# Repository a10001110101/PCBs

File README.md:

# PCBs
Various gerbers and other files for PCB design

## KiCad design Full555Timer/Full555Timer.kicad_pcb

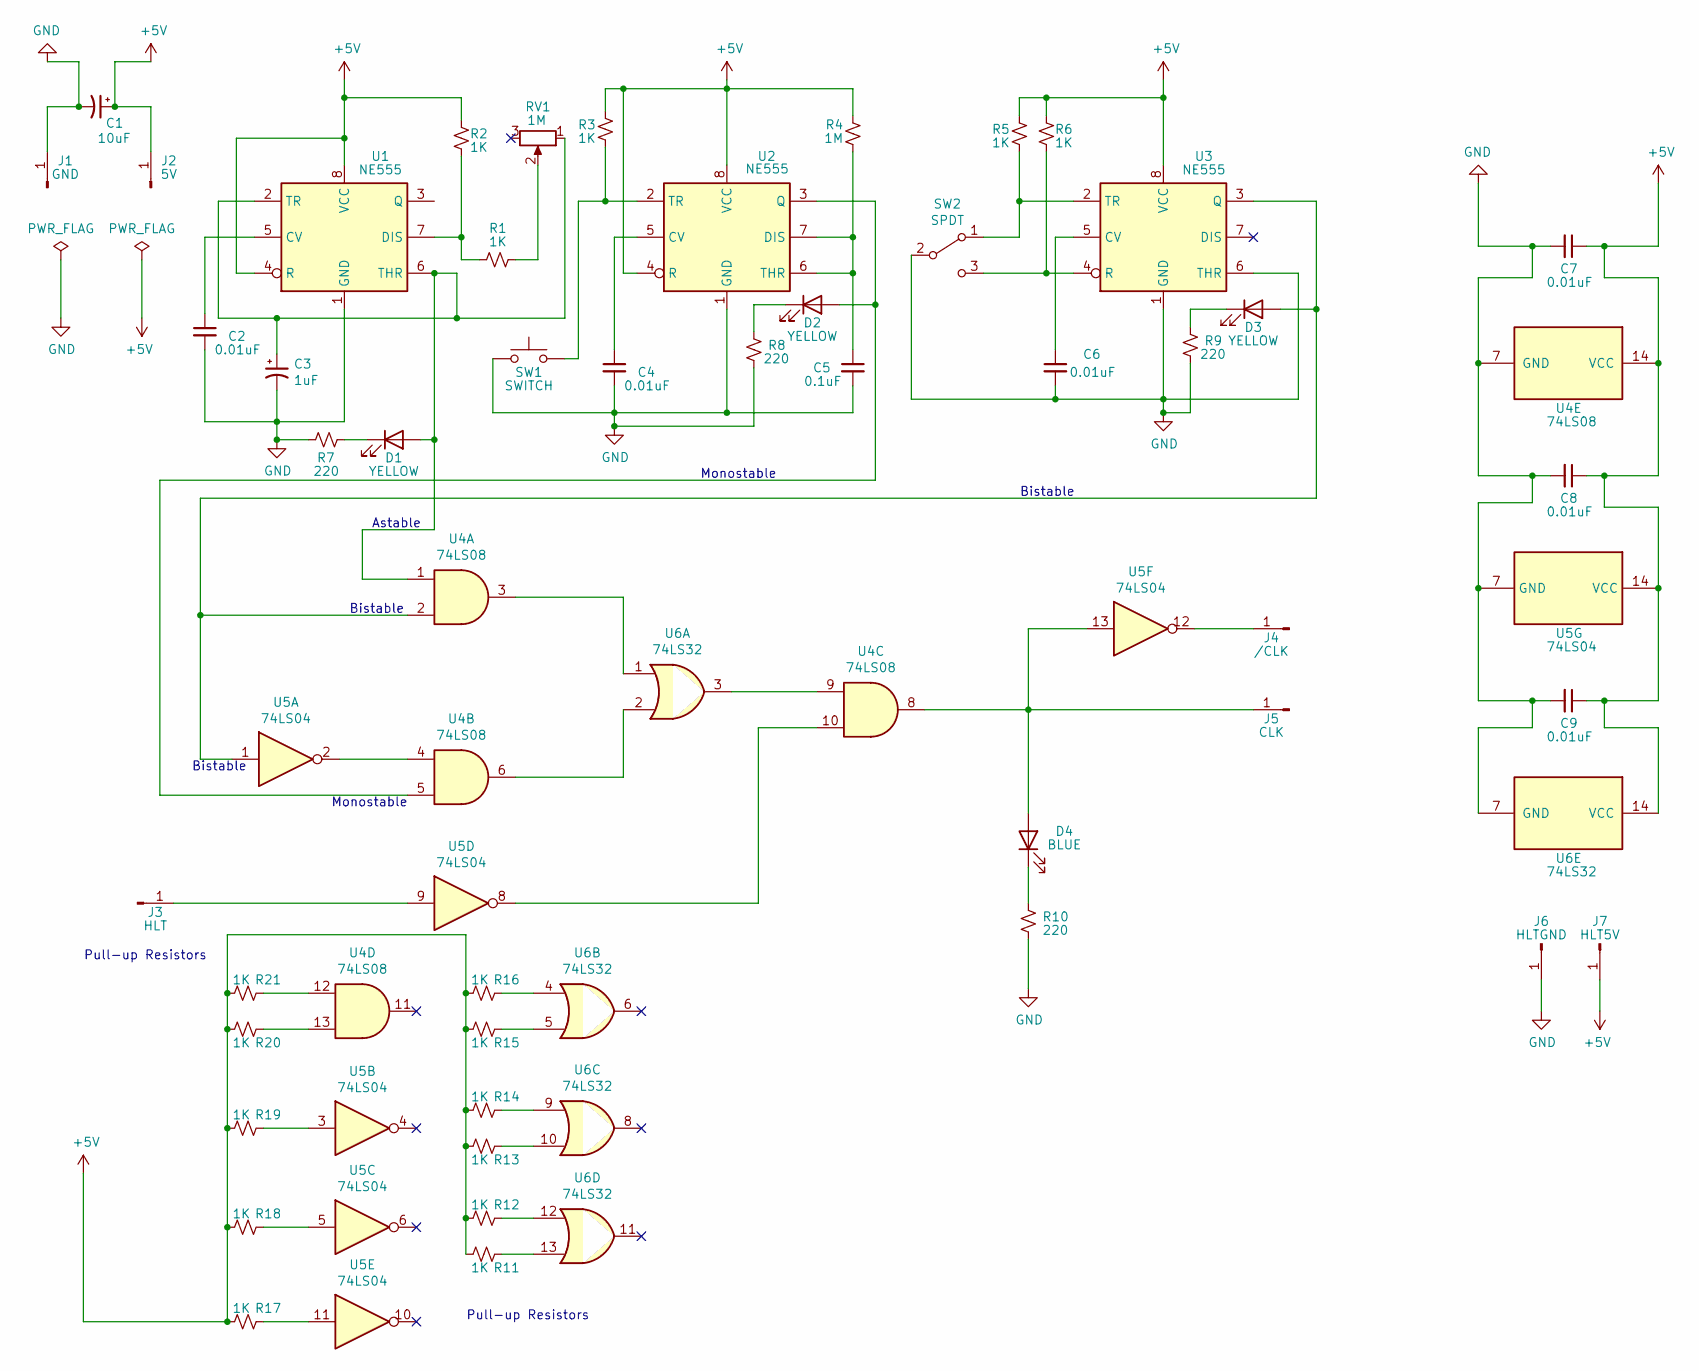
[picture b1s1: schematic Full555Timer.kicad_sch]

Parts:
C1: 10uF; CP_Radial_D6.3mm_P2.50mm
C2, C4, C6, C7, C8, C9: 0.01uF; C_Disc_D6.0mm_W2.5mm_P5.00mm
C3: 1uF; CP_Radial_D5.0mm_P2.50mm
C5: 0.1uF; C_Disc_D4.7mm_W2.5mm_P5.00mm
D1, D2, D3: YELLOW; LED_D3.0mm
D4: BLUE; LED_D3.0mm
J1: GND; PinHeader_1x01_P1.00mm_Vertical
J2: 5V; PinHeader_1x01_P1.00mm_Vertical
J3: HLT; PinHeader_1x01_P1.00mm_Vertical
J4: /CLK; PinHeader_1x01_P1.00mm_Vertical
J5: CLK; PinHeader_1x01_P1.00mm_Vertical
J6: HLTGND; PinHeader_1x01_P1.00mm_Vertical
J7: HLT5V; PinHeader_1x01_P1.00mm_Vertical
R1, R2, R3, R5, R6, R11, R12, R13, R14, R15, R16, R17, R18, R19, R20, R21: 1K; R_Axial_DIN0207_L6.3mm_D2.5mm_P10.16mm_Horizontal
R4: 1M; R_Axial_DIN0207_L6.3mm_D2.5mm_P10.16mm_Horizontal
R7, R8, R9, R10: 220; R_Axial_DIN0207_L6.3mm_D2.5mm_P10.16mm_Horizontal
RV1: 1M; Potentiometer_Bourns_3386C_Horizontal
SW1: SWITCH; B3F-1000
SW2: SPDT; SW_SS-12E17
U1, U2, U3: NE555; DIP-8_W7.62mm
U4: 74LS08; DIP-14_W7.62mm
U5: 74LS04; DIP-14_W7.62mm
U6: 74LS32; DIP-14_W7.62mm

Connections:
+5V: C1.1, C7.1, C8.1, C9.1, J2.1, J7.1, R2.2, R3.2, R4.2, R5.2, R6.2, R11.2, R12.2, R13.2, R14.2, R15.2, R16.2, R17.2, R18.2, R19.2, R20.2, R21.2, U1.4 (R), U1.8 (VCC), U2.4 (R), U2.8 (VCC), U3.8 (VCC), U4.14 (VCC), U5.14 (VCC), U6.14 (VCC)
GND: C1.2, C2.2, C3.2, C4.2, C5.2, C6.2, C7.2, C8.2, C9.2, J1.1, J6.1, R7.1, R8.2, R9.2, R10.2, SW1.1, SW2.2 (B), U1.1 (GND), U2.1 (GND), U3.1 (GND), U3.6 (THR), U4.7 (GND), U5.7 (GND), U6.7 (GND)
unnamed: C2.1, U1.5 (CV)
unnamed: C4.1, U2.5 (CV)
unnamed: C5.1, R4.1, U2.6 (THR), U2.7 (DIS)
unnamed: C6.1, U3.5 (CV)
unnamed: D1.1 (K), R7.2
unnamed: D2.1 (K), R8.1
unnamed: D2.2 (A), U2.3 (Q), U4.5
unnamed: D3.1 (K), R9.1
unnamed: D3.2 (A), U3.3 (Q), U4.2, U5.1
unnamed: D4.1 (K), R10.1
unnamed: D4.2 (A), J5.1, U4.8, U5.13
unnamed: J3.1, U5.9
unnamed: J4.1, U5.12
unnamed: R1.1, RV1.2
unnamed: R1.2, R2.1, U1.7 (DIS)
unnamed: R3.1, SW1.2, U2.2 (TR)
unnamed: R5.1, SW2.1 (A), U3.2 (TR)
unnamed: R6.1, SW2.3 (C), U3.4 (R)
unnamed: R11.1, U6.13
unnamed: R12.1, U6.12
unnamed: R13.1, U6.10
unnamed: R14.1, U6.9
unnamed: R15.1, U6.5
unnamed: R16.1, U6.4
unnamed: R17.1, U5.11
unnamed: R18.1, U5.5
unnamed: R19.1, U5.3
unnamed: R20.1, U4.13
unnamed: R21.1, U4.12
unnamed: U4.3, U6.1
unnamed: U4.4, U5.2
unnamed: U4.6, U6.2
unnamed: U4.9, U6.3
unnamed: U4.10, U5.8

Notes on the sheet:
Monostable
Astable
Bistable
Pull-up Resistors

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
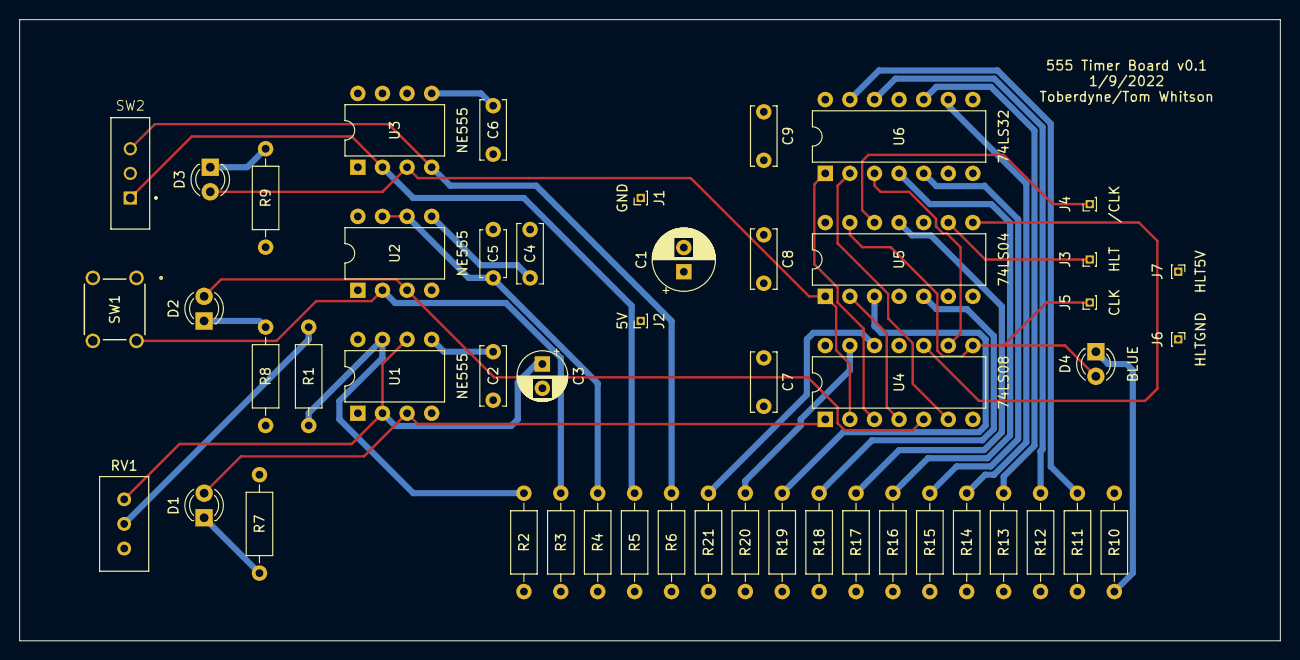
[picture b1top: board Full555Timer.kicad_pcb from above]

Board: 4 copper layers, 130.2 x 64.1 mm, 50 parts (0 on the bottom side), 38 nets.

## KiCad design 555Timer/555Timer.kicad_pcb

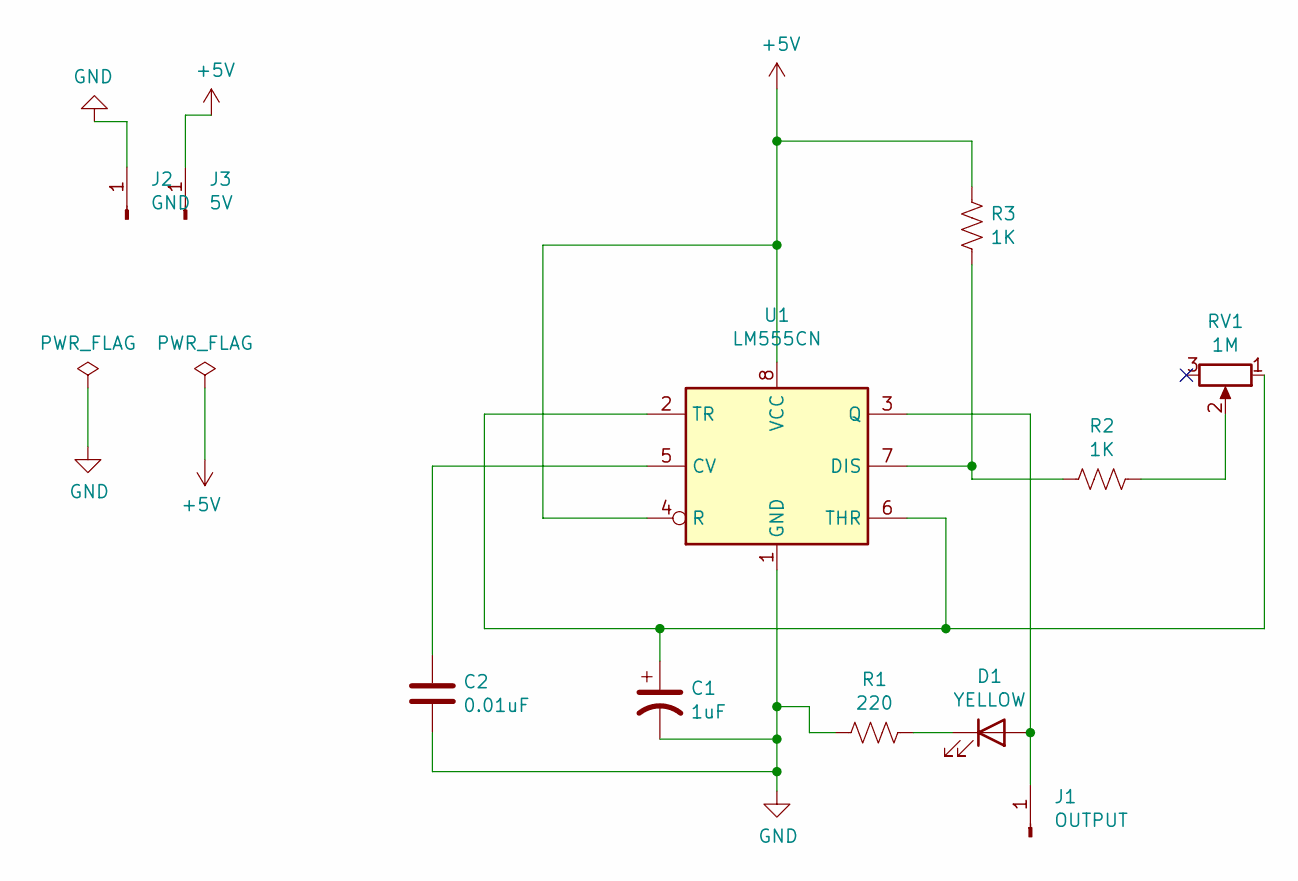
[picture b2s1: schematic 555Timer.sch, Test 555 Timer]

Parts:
C1: 1uF; CP_Radial_D5.0mm_P2.50mm
C2: 0.01uF; C_Disc_D6.0mm_W2.5mm_P5.00mm
D1: YELLOW; LED_D5.0mm
J1: OUTPUT; PinHeader_1x01_P1.00mm_Vertical
J2: GND; PinHeader_1x01_P2.54mm_Vertical
J3: 5V; PinHeader_1x01_P1.00mm_Vertical
R1: 220; R_Axial_DIN0207_L6.3mm_D2.5mm_P10.16mm_Horizontal
R2, R3: 1K; R_Axial_DIN0207_L6.3mm_D2.5mm_P10.16mm_Horizontal
RV1: 1M; Potentiometer_Bourns_3386C_Horizontal
U1: LM555CN; DIP-8_W7.62mm

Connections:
+5V: J3.1, R3.1, U1.4 (R), U1.8 (VCC)
GND: C1.2, C2.2, J2.1, R1.1, U1.1 (GND)
unnamed: C1.1, RV1.1, U1.2 (TR), U1.6 (THR)
unnamed: C2.1, U1.5 (CV)
unnamed: D1.1 (K), R1.2
unnamed: D1.2 (A), J1.1, U1.3 (Q)
unnamed: R2.1, RV1.2
unnamed: R2.2, R3.2, U1.7 (DIS)

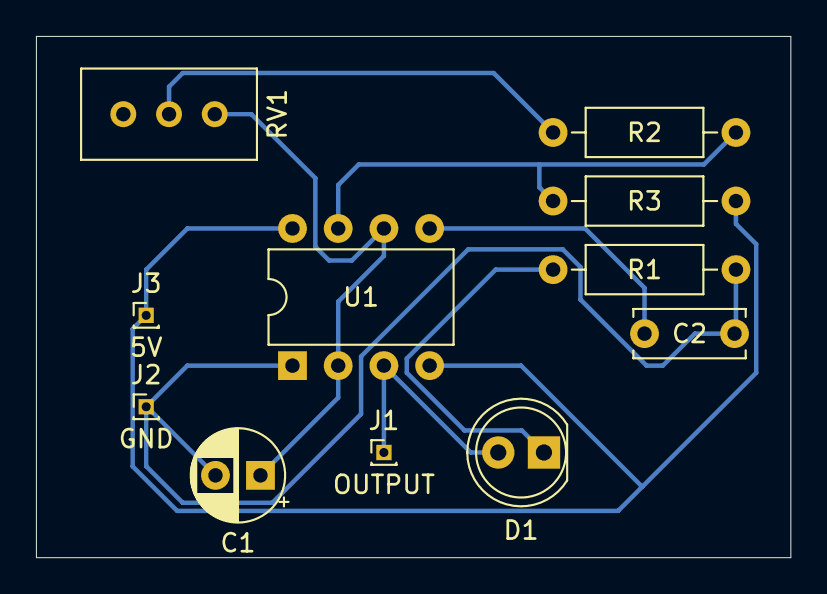
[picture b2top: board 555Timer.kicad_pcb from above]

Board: 2 copper layers, 41.9 x 29.0 mm, 11 parts (0 on the bottom side), 8 nets.

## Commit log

2021-10-29 Update LICENSE
